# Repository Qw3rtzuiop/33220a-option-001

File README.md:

# 33220a-option-001
External reference frequency option for the HP/Agilent/Keysight 33220a arbitrary function generator.

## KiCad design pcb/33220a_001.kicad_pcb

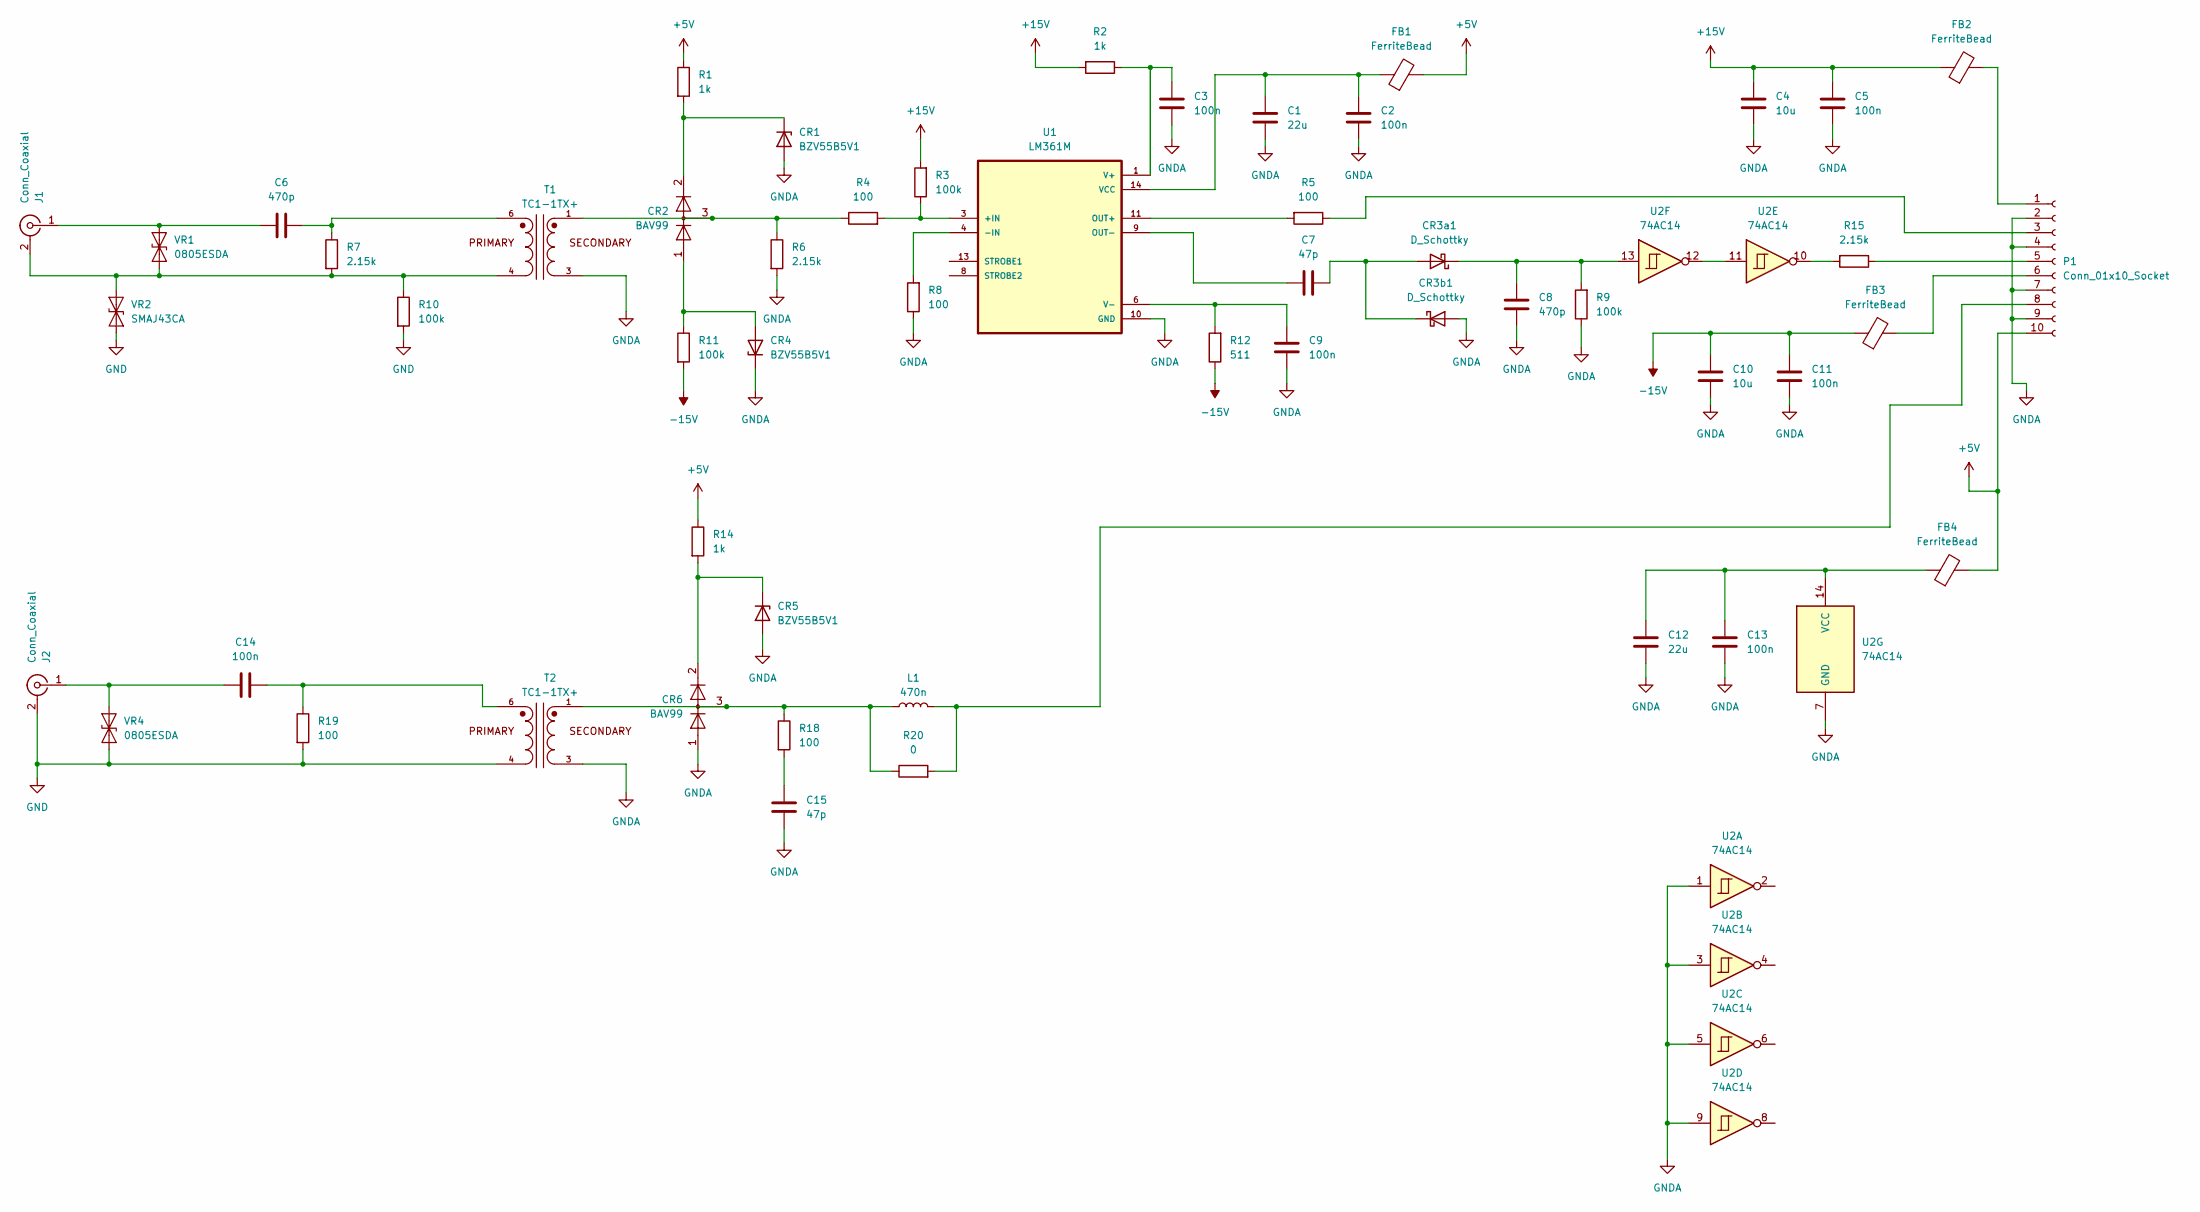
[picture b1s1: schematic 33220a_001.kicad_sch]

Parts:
C1, C12: 22u; C_0805_2012Metric
C2, C3, C5, C9, C11, C13, C14: 100n; C_0805_2012Metric
C4, C10: 10u; C_0805_2012Metric
C6, C8: 470p; C_0805_2012Metric
C7, C15: 47p; C_0805_2012Metric
CR1, CR4, CR5: BZV55B5V1; D_MiniMELF
CR2, CR6: BAV99; SOT-23
CR3a1, CR3b1: D_Schottky; D_SOD-523
FB1, FB2, FB3, FB4: FerriteBead; L_0805_2012Metric
J1, J2: Conn_Coaxial; BNC_Amphenol_B6252HB-NPP3G-50_Horizontal
L1: 470n; L_0805_2012Metric
P1: Conn_01x10_Socket; IDC-Header_2x05_P2.54mm_Vertical
R1, R2, R14: 1k; R_0805_2012Metric
R3, R9, R10, R11: 100k; R_0805_2012Metric
R4, R5, R8, R18, R19: 100; R_0805_2012Metric
R6, R7, R15: 2.15k; R_0805_2012Metric
R12: 511; R_0805_2012Metric
R20: 0; R_0805_2012Metric
T1, T2: TC1-1TX+; XFMR_TC1-1-13M_; PARTREV F
U1: LM361M; SOIC-14_3.9x8.7mm_P1.27mm
U2: 74AC14; SOIC-14_3.9x8.7mm_P1.27mm
VR1, VR4: 0805ESDA; D_SOD-523
VR2: SMAJ43CA; D_SMA

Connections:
+5V: FB1.2, FB4.2, P1.10, R1.1, R14.1
+15V: C4.2, C5.2, FB2.1, R2.2, R3.2
-15V: C10.2, C11.2, FB3.1, R11.2, R12.1
GND: J2.2 (Ext), R10.2, R19.2, T2.4, VR2.1 (A1), VR4.1 (A1)
GNDA: C1.1, C2.1, C3.1, C4.1, C5.1, C8.1, C9.1, C10.1, C11.1, C12.1, C13.1, C15.1, CR1.2 (A), CR3b1.2 (A), CR4.1 (K), CR5.2 (A), CR6.1 (K), P1.2, P1.4, P1.7, P1.9, R6.2, R8.1, R9.1, T1.3, T2.3, U1.10 (GND), U2.1, U2.3, U2.5, U2.7 (GND), U2.9
unnamed: C6.2, R7.1, T1.6
unnamed: C14.2, R19.1, T2.6
unnamed: C15.2, R18.2
unnamed: CR1.1 (K), CR2.2 (A), R1.2
unnamed: CR2.3 (K), R4.1, R6.1, T1.1
unnamed: C7.1, CR3a1.2 (A), CR3b1.1 (K)
unnamed: C8.2, CR3a1.1 (K), R9.2, U2.13
unnamed: CR2.1 (K), CR4.2 (A), R11.1
unnamed: CR5.1 (K), CR6.2 (A), R14.2
unnamed: CR6.3 (K), L1.1, R18.1, R20.1, T2.1
unnamed: J1.2 (Ext), R7.2, R10.1, T1.4, VR1.1 (A1), VR2.2 (A2)
unnamed: C6.1, J1.1 (In), VR1.2 (A2)
unnamed: C14.1, J2.1 (In), VR4.2 (A2)
unnamed: FB2.2, P1.1
unnamed: P1.3, R5.1
unnamed: P1.5, R15.1
unnamed: FB3.2, P1.6
unnamed: L1.2, P1.8, R20.2
unnamed: R15.2, U2.10
unnamed: R3.1, R4.2, U1.3 (+IN)
unnamed: R8.2, U1.4 (-IN)
unnamed: R5.2, U1.11 (OUT+)
unnamed: C7.2, U1.9 (OUT-)
unnamed: C3.2, R2.1, U1.1 (V+)
unnamed: C9.2, R12.2, U1.6 (V-)
unnamed: C1.2, C2.2, FB1.1, U1.14 (VCC)
unnamed: U2.11, U2.12
unnamed: C12.2, C13.2, FB4.1, U2.14 (VCC)

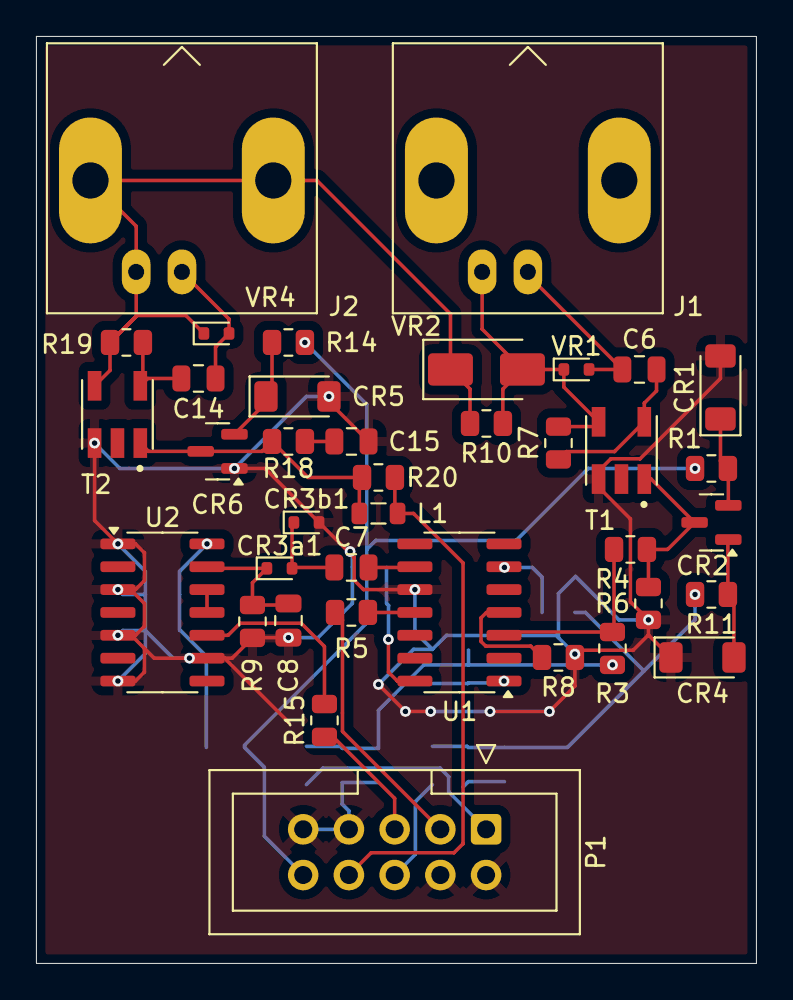
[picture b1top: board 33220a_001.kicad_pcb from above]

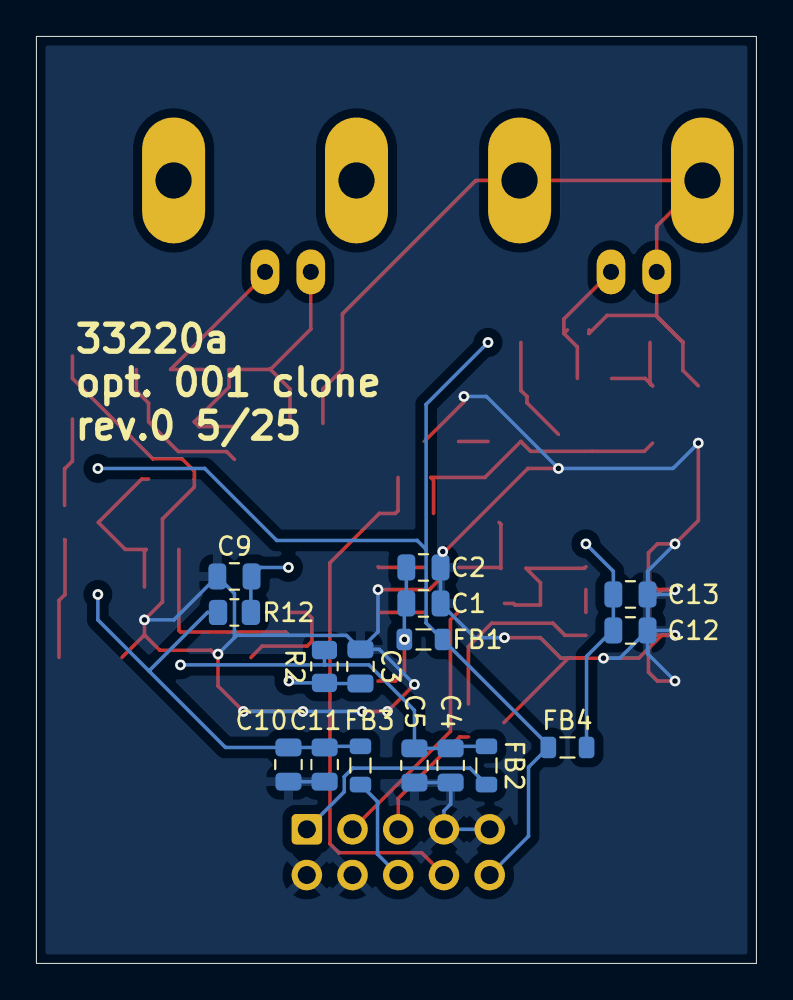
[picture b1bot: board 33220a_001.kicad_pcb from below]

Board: 2 copper layers, 40.0 x 51.5 mm, 54 parts (16 on the bottom side), 33 nets.

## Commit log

2025-05-24 rev.0
2025-06-15 added pics and added units
